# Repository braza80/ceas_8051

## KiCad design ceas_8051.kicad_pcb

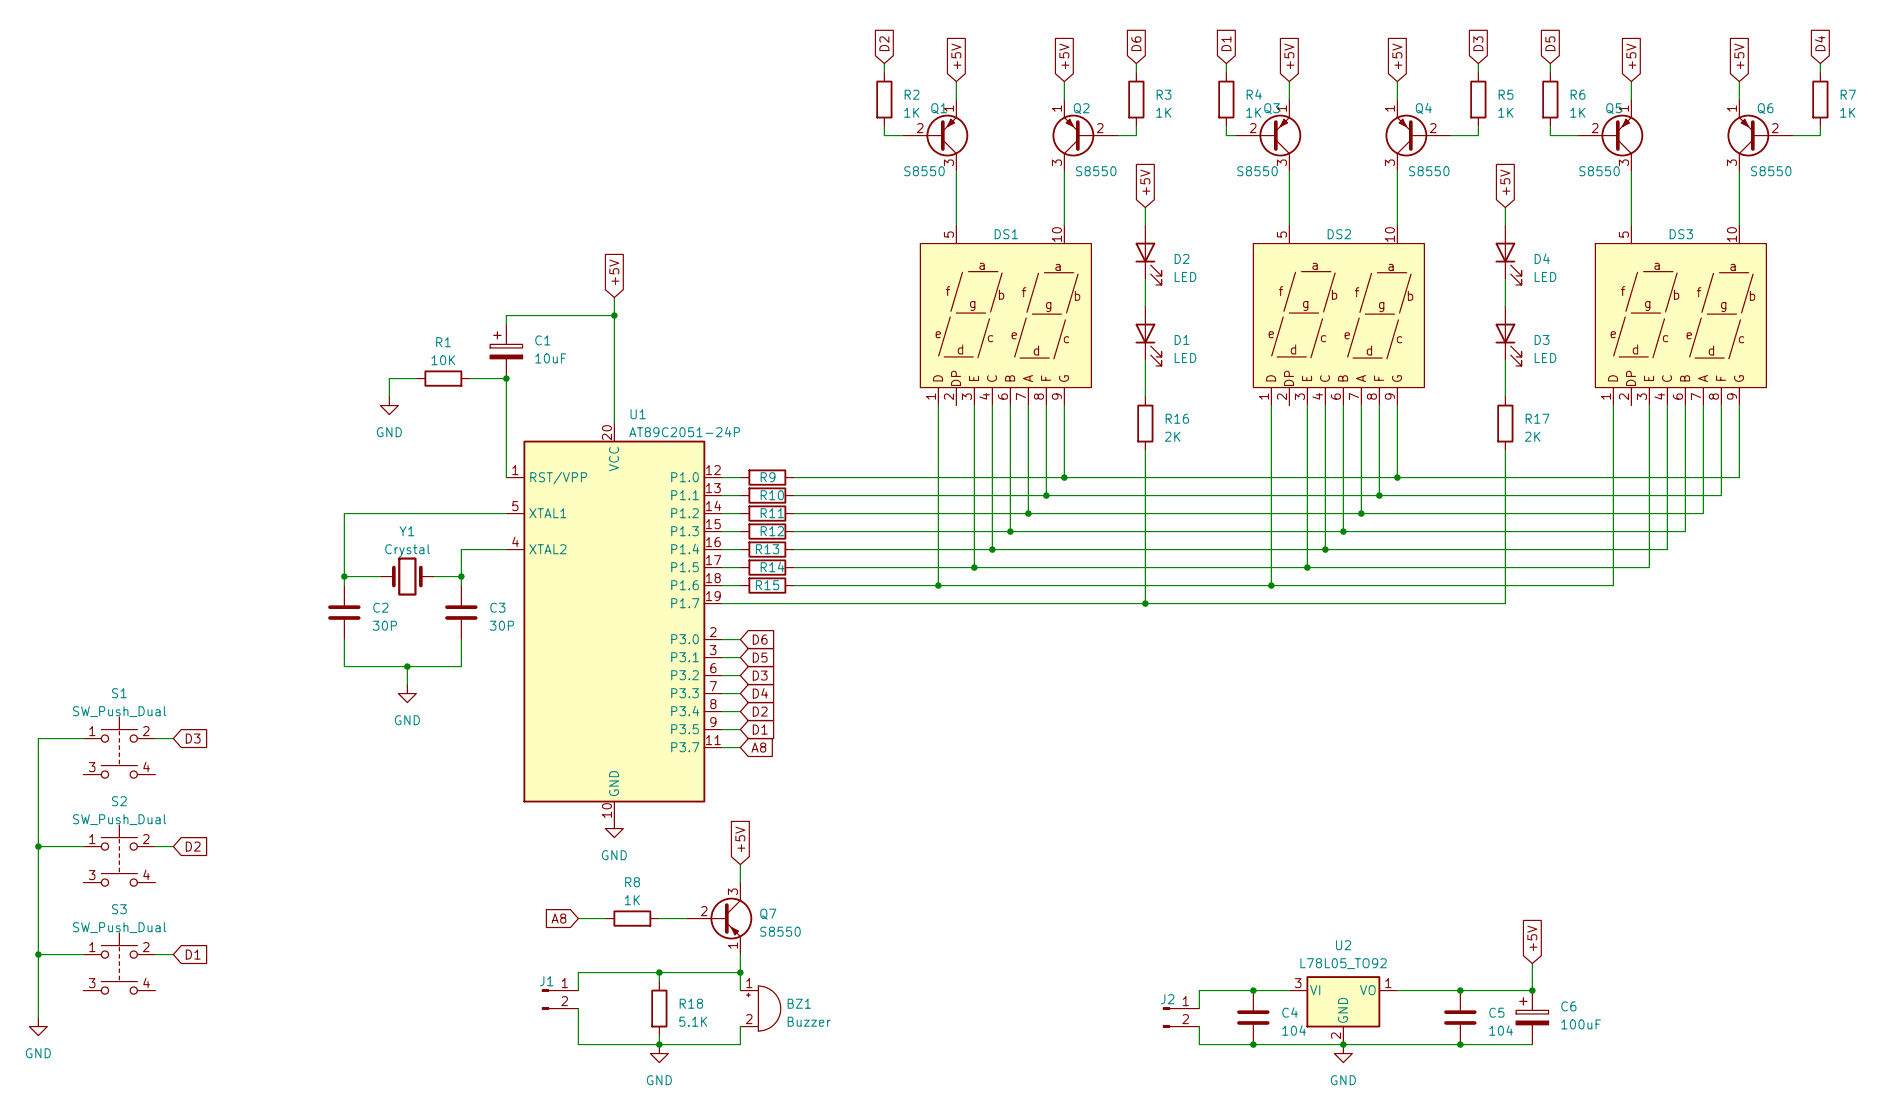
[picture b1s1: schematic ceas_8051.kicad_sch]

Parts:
BZ1: Buzzer; MagneticBuzzer_Kingstate_KCG0601
C1: 10uF; CP_Radial_D4.0mm_P2.00mm
C2, C3: 30P; C_Disc_D3.4mm_W2.1mm_P2.50mm
C4, C5: 104; C_Disc_D3.4mm_W2.1mm_P2.50mm
C6: 100uF; CP_Radial_D5.0mm_P2.50mm
D1, D2, D3, D4: LED; LED_D3.0mm
DS1, DS3: ELD_426XXXX
DS2: 3261BS
J1, J2: Conn_01x02_Pin; PinHeader_1x02_P1.00mm_Vertical
Q1, Q2, Q3, Q4, Q5, Q6, Q7: S8550; TO-92_Inline
R1: 10K; R_Axial_DIN0204_L3.6mm_D1.6mm_P7.62mm_Horizontal
R2, R3, R4, R5, R6, R7, R8, R9, R10, R11, R12, R13, R14, R15: 1K; R_Axial_DIN0204_L3.6mm_D1.6mm_P7.62mm_Horizontal
R16, R17: 2K; R_Axial_DIN0204_L3.6mm_D1.6mm_P7.62mm_Horizontal
R18: 5.1K; R_Axial_DIN0204_L3.6mm_D1.6mm_P7.62mm_Horizontal
S1, S2, S3: SW_Push_Dual; SW_PUSH_6mm_H8mm
U1: AT89C2051-24P; DIP-20_W7.62mm
U2: L78L05_TO92; TO-92_Inline
Y1: Crystal; Crystal_HC18-U_Vertical

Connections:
+5V: C1.1, C5.1, C6.1, D2.2 (A), D4.2 (A), Q1.1 (E), Q2.1 (E), Q3.1 (E), Q4.1 (E), Q5.1 (E), Q6.1 (E), Q7.3 (C), U1.20 (VCC), U2.1 (VO)
A8: R8.1, U1.11 (P3.7)
D1: R4.1, S3.2, U1.9 (P3.5)
D2: R2.1, S2.2, U1.8 (P3.4)
D3: R5.1, S1.2, U1.6 (P3.2)
D4: R7.1, U1.7 (P3.3)
D5: R6.1, U1.3 (P3.1)
D6: R3.1, U1.2 (P3.0)
GND: BZ1.2 (+), C2.2, C3.2, C4.2, C5.2, C6.2, J1.2, J2.2, R1.1, R18.2, S1.1, S2.1, S3.1, U1.10 (GND), U2.2 (GND)
unnamed: BZ1.1 (-), J1.1, Q7.1 (E), R18.1
unnamed: D1.2 (A), D2.1 (K)
unnamed: D1.1 (K), R16.1
unnamed: D3.2 (A), D4.1 (K)
unnamed: D3.1 (K), R17.1
unnamed: DS1.1, DS2.1, DS3.1, R15.1
unnamed: DS1.3, DS2.3, DS3.3, R14.1
unnamed: DS1.4, DS2.4, DS3.4, R13.1
unnamed: DS1.6, DS2.6, DS3.6, R12.1
unnamed: DS1.7, DS2.7, DS3.7, R11.1
unnamed: DS1.8, DS2.8, DS3.8, R10.1
unnamed: DS1.9, DS2.9, DS3.9, R9.1
unnamed: C4.1, J2.1, U2.3 (VI)
unnamed: Q1.2 (B), R2.2
unnamed: DS1.5, Q1.3 (C)
unnamed: Q2.2 (B), R3.2
unnamed: DS1.10, Q2.3 (C)
unnamed: Q3.2 (B), R4.2
unnamed: DS2.5, Q3.3 (C)
unnamed: Q4.2 (B), R5.2
unnamed: DS2.10, Q4.3 (C)
unnamed: Q5.2 (B), R6.2
unnamed: DS3.5, Q5.3 (C)
unnamed: Q6.2 (B), R7.2
unnamed: DS3.10, Q6.3 (C)
unnamed: Q7.2 (B), R8.2
unnamed: R9.2, U1.12 (P1.0)
unnamed: R10.2, U1.13 (P1.1)
unnamed: R11.2, U1.14 (P1.2)
unnamed: R12.2, U1.15 (P1.3)
unnamed: R13.2, U1.16 (P1.4)
unnamed: R14.2, U1.17 (P1.5)
unnamed: R15.2, U1.18 (P1.6)
unnamed: R16.2, R17.2, U1.19 (P1.7)
unnamed: C1.2, R1.2, U1.1 (RST/VPP)
unnamed: C2.1, U1.5 (XTAL1), Y1.1
unnamed: C3.1, U1.4 (XTAL2), Y1.2

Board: 2 copper layers, 47 parts (0 on the bottom side), 46 nets, no tracks yet.

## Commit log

2023-02-25 Saved version
    Shitty PCB
